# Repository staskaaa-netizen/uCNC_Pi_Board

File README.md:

# uCNC RP2350B Motherboard - MANUFACTURING-READY PROTOTYPE

KiCad 10 carrier for a socketed WeAct Studio RP2350B Core Board. The board
provides isolated machine I/O, motion and encoder interfaces, LCD power,
storage, optional Wi-Fi and analog I/O on a 160 mm x 120 mm two-layer PCB.

**Status: MANUFACTURING PACKAGE GENERATED; FINAL DRC REVIEW REQUIRED.** The
circuit, pin mapping, PCB and manufacturing archives are complete. The PCB
fabrication and SMT assembly ZIPs are generated from the current board.

The current BOM has 263 physical parts in 44 purchasing groups. SMT assembly
contains 227 references in 33 groups; D53 is hand-fit and excluded from the
CPL. The combined JLC BOM contains 262 references in 43 groups.

## Board features

- 16 isolated 24 V PLC inputs, `I01-I16`, with TLP291-4 optocouplers.
- One dedicated isolated E-stop input on GPIO9, outside the shift-register
  chain.
- Four cascaded 74HC165 inputs and four cascaded SN74AHCT595 outputs.
- All 32 input-register channels have 10 k pull-ups, including the direct
  servo ZERO/ERROR inputs.
- Seven STEP/DIR axes, A0-A6, with labels `EN3 STPn DIRn`.
- Seven paired servo ZERO/ERROR inputs with individual 3-pin connectors.
- Two spare U7 register inputs exposed on J55 with 10 k pull-ups.
- All 35 indicator LEDs are green Hubei KENTO `KT-0805G` 0805 parts.
- Two onsemi MC74AC541DWR2G 5 V motion buffers.
- Sixteen optically isolated general outputs, `D01-D16`, driven by two
  TBD62083AFG(Z,EL) arrays.
- Three 5 V encoder interfaces with a 3.3 V logic-side buffer.
- Four 0-10 V analog inputs and four ground-referenced 0-10 V analog outputs.
- MicroSD through J36 or the on-board SOFNG TF-15x15 socket J54.
- Passive HSTX-to-LVDS interface on J22 using two 4 x 330 ohm, 4 x 0603 arrays.
- Optional ESP-01 with a dedicated 3.3 V regulator.
- Isolated 24 V to 12 V backlight supply.

## I/O map

| Function | Signal | Connector mapping |
|---|---|---|
| PLC inputs | `I01-I16` | J7: `I01-I08`; J8: `I09-I16` |
| General outputs | `D01-D16` | J12: `D01-D08`; J32: `D09-D16` |
| Motion A0 | `EN3`, `STP0`, `DIR0` | J10; status J40 |
| Motion A1 | `EN3`, `STP1`, `DIR1` | J11; status J41 |
| Motion A2 | `EN3`, `STP2`, `DIR2` | J28; status J42 |
| Motion A3 | `EN4`, `STP3`, `DIR3` | J29; status J43 |
| Motion A4 | `EN4`, `STP4`, `DIR4` | J47; status J50 |
| Motion A5 | `EN4`, `STP5`, `DIR5` | J46; status J49 |
| Motion A6 | `EN4`, `STP6`, `DIR6` | J30; status J48 |

The isolated logic-side input names are `I01_N-I16_N`. Every motion connector
uses pin 1 for enable, pin 2 for STEP and pin 3 for DIR. Every paired status
connector uses pin 1 for `GND`, pin 2 for ERROR and pin 3 for ZERO.
On the assembled board, motion labels are printed in the opposite physical
reading direction as `DIRn STPn ENx`; the pad-to-net mapping above remains
authoritative.

## Open the project

Open `hardware/motherboard.kicad_pro` in KiCad 10.0 or newer.

- Root schematic: `hardware/motherboard.kicad_sch`
- PCB: `hardware/motherboard.kicad_pcb`
- Local symbols, footprints and 3D models: `hardware/libraries/`
- Manufacturing data: `manufacturing/` (see `manufacturing/README.md`)
- Design notes: `documentation/`

The checked-in KiCad board is authoritative. It contains the approved manual
placement and routing. Do not run a full PCB regeneration over that file.

## Design documentation

- [Board specification](documentation/board-specification.md)
- [GPIO map](documentation/gpio-map.md)
- [Normative HAL pin and function contract](documentation/hal-pinout-contract.md)
- [WeAct RP2350B pin allocation](documentation/rp2350-pinout.md)
- [Input and output bit map](documentation/io-bit-map.md)
- [Signal naming](documentation/naming.md)
- [Connector pinouts](documentation/connectors.md)
- [Power budget](documentation/power-budget.md)
- [PLC inputs](documentation/plc-inputs.md)
- [Decoupling map](documentation/decoupling-map.md)
- [Component placement classes](documentation/component-placement-classes.md)
- [LCD LVDS interface](documentation/display-population.md)
- [Wi-Fi module](documentation/wifi-module.md)
- [Analog calibration](documentation/analog-calibration.md)
- [Four-channel 0-10 V outputs](documentation/analog-outputs.md)
- [uCNC RP2350 compatibility](documentation/ucnc-rp2350.md)
- [Mechanical notes](documentation/mechanical.md)
- [Assembly notes](documentation/assembly-options.md)
- [Release checklist](TODO.md)
- [Design-process retrospective and next-time playbook](documentation/design-process-retrospective.md)

## Manufacturing review files

- [Combined board review](manufacturing/board-review.pdf)
- [Ordered first-batch PCB review](manufacturing/board-ordered-first-batch.jpg)
- [Board specification PDF](manufacturing/board-specification.pdf)
- [Front artwork and assembly layer](manufacturing/board-front.pdf)
- [Mirrored rear artwork](manufacturing/board-back.pdf)
- [Current top 3D render](manufacturing/board-3d-top-da42d9de.png)
- [Current bottom 3D render](manufacturing/board-3d-bottom-da42d9de.png)
- [Connector label orientation check](manufacturing/connector-label-check.png)
- [Complete grouped BOM](manufacturing/bom.csv)
- [SMT-only grouped BOM](manufacturing/bom-smt.csv)
- [SMT-only reference BOM](manufacturing/bom-smt-refs.csv)
- [JLCPCB-format grouped BOM](manufacturing/bom-jlcpcb.csv)
- [JLCPCB stock and Basic/Extended audit](manufacturing/jlcpcb-stock-audit.csv)
- [Non-SMT grouped BOM](manufacturing/bom-non-smt.csv)
- [Combined SMT and non-SMT BOM](manufacturing/bom-all-jlcpcb.csv)
- [Pick-and-place CPL](manufacturing/cpl-jlcpcb.csv)
- [PCB fabrication ZIP](manufacturing/uCNC_Pi_Board_PCB_Fabrication.zip)
- [PCB fabrication + SMT assembly ZIP](manufacturing/uCNC_Pi_Board_SMT_Assembly.zip)

## Verification status

The current netlist contains 274 schematic components in 321 nets. The PCB has
268 footprints, 2,221 routed track segments and 232 vias. DRC reports zero
unconnected items, no copper-clearance errors and eight silkscreen warnings.
ERC has no electrical errors and 35 library-symbol cache warnings.

This is a routed prototype manufacturing package. It is not a safety-rated
controller. Hazardous energy removal must remain an independent hard-wired
safety function and must be validated in the complete machine.

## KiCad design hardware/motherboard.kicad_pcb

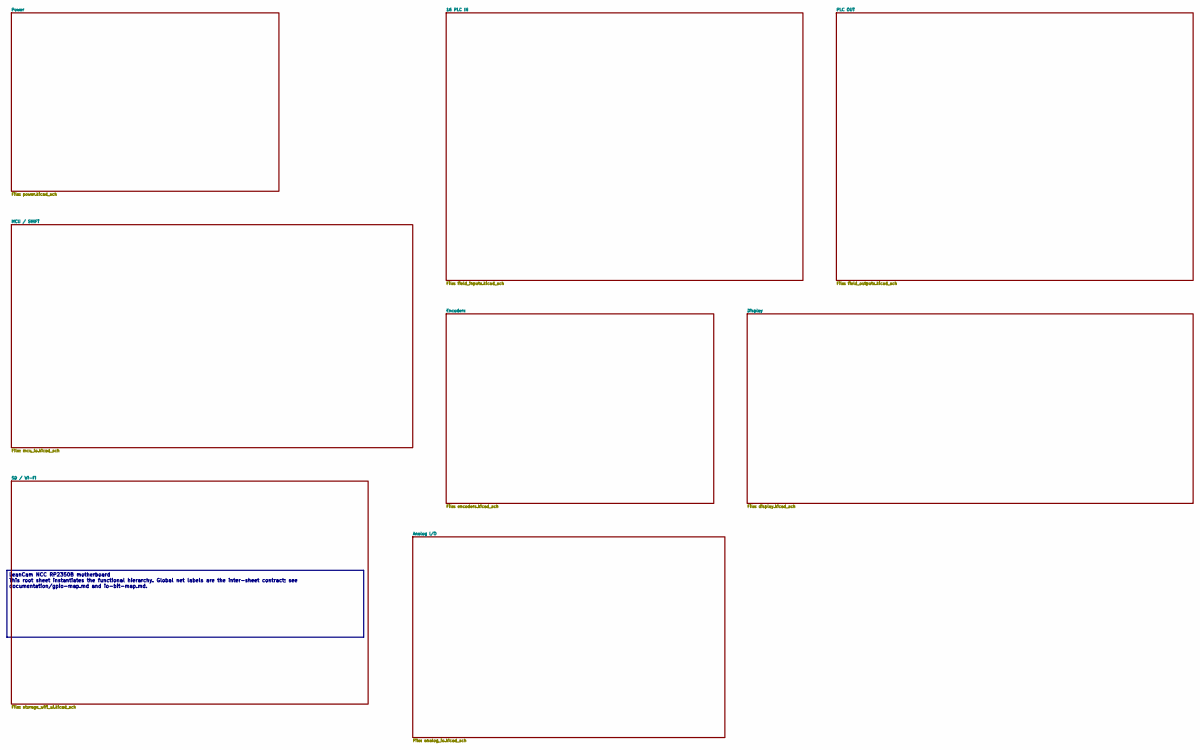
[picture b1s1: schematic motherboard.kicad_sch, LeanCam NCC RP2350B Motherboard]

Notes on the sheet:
LeanCam NCC RP2350B motherboard This root sheet instantiates the functional hierarchy. Global net labels are the inter-sheet contract; see documentation/gpio-map.md and io-bit-map.md.

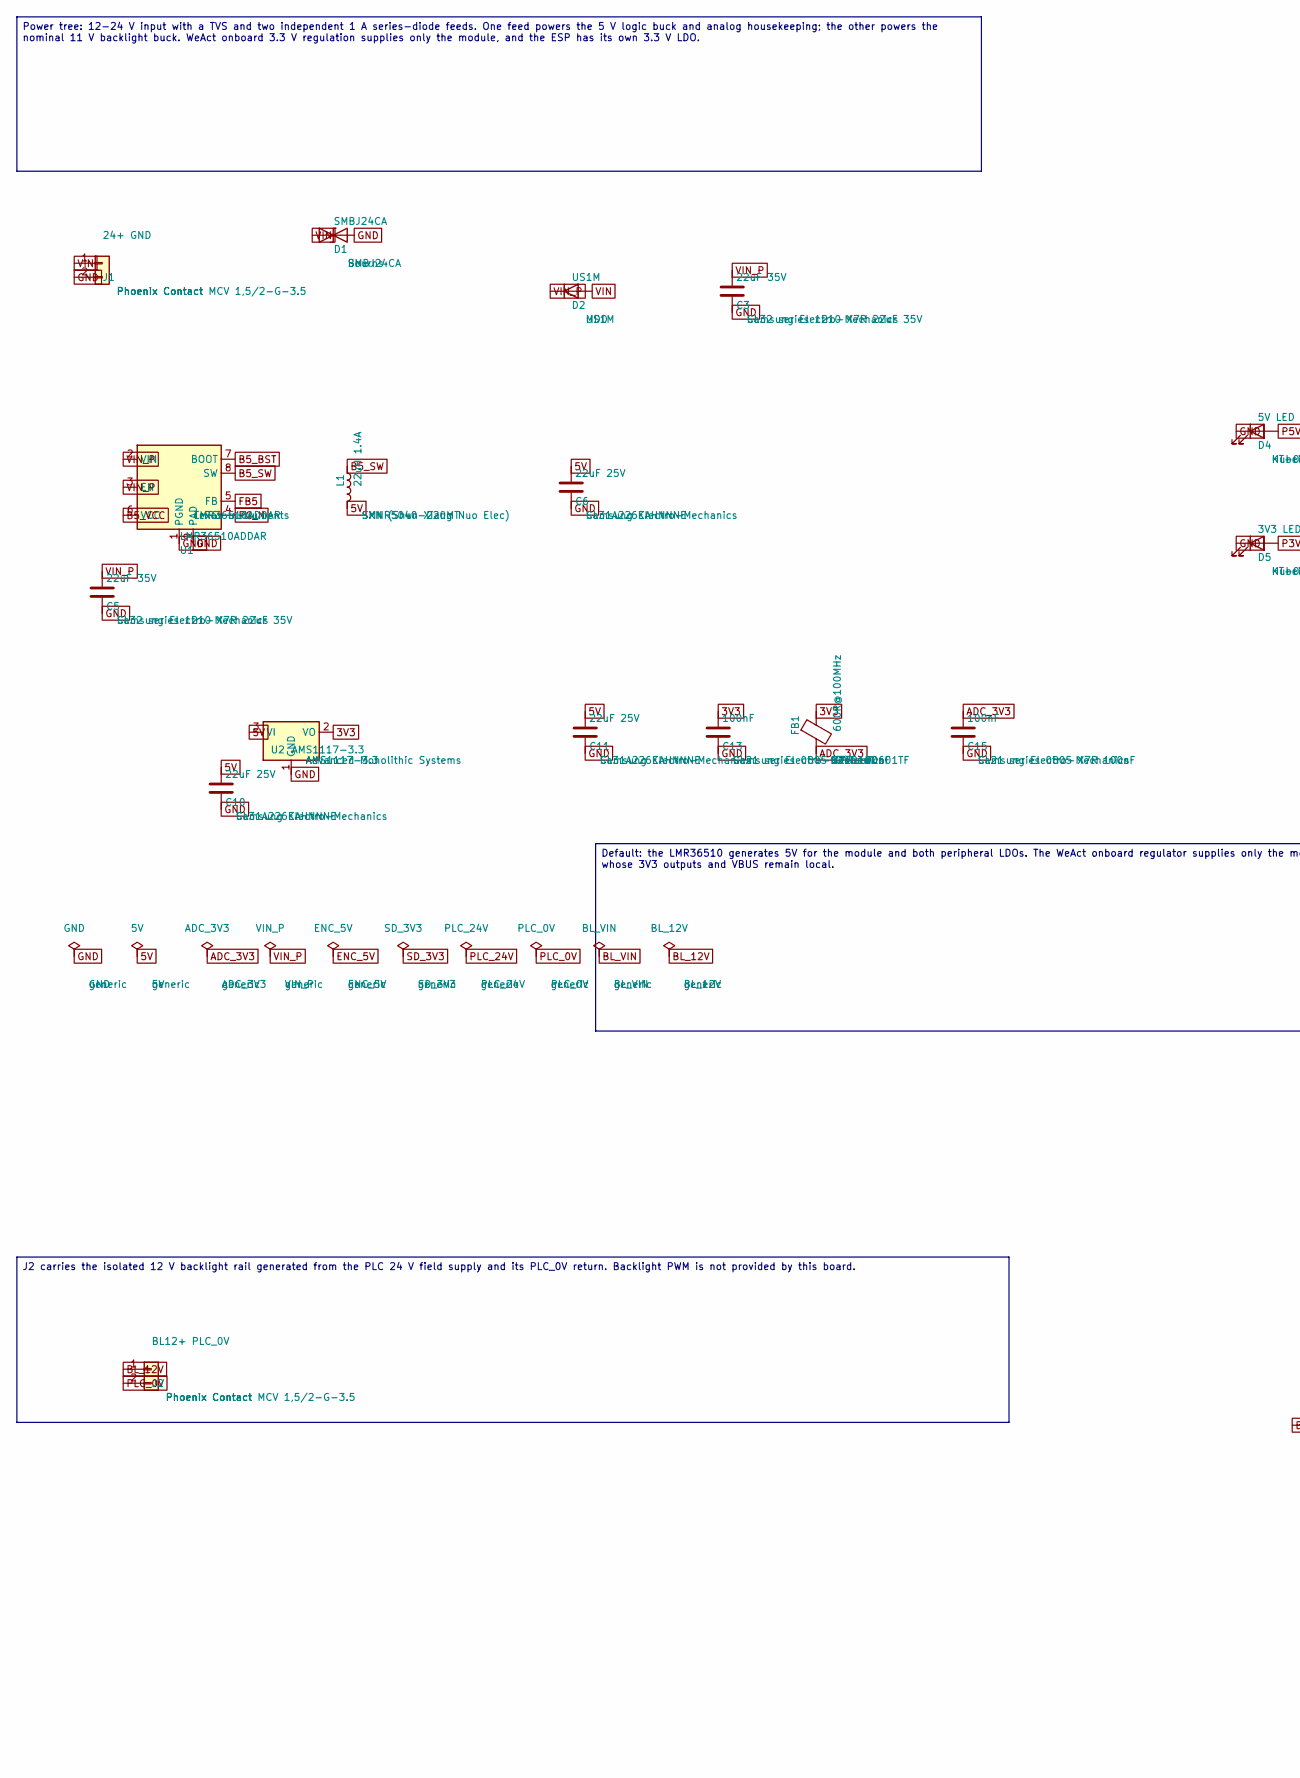
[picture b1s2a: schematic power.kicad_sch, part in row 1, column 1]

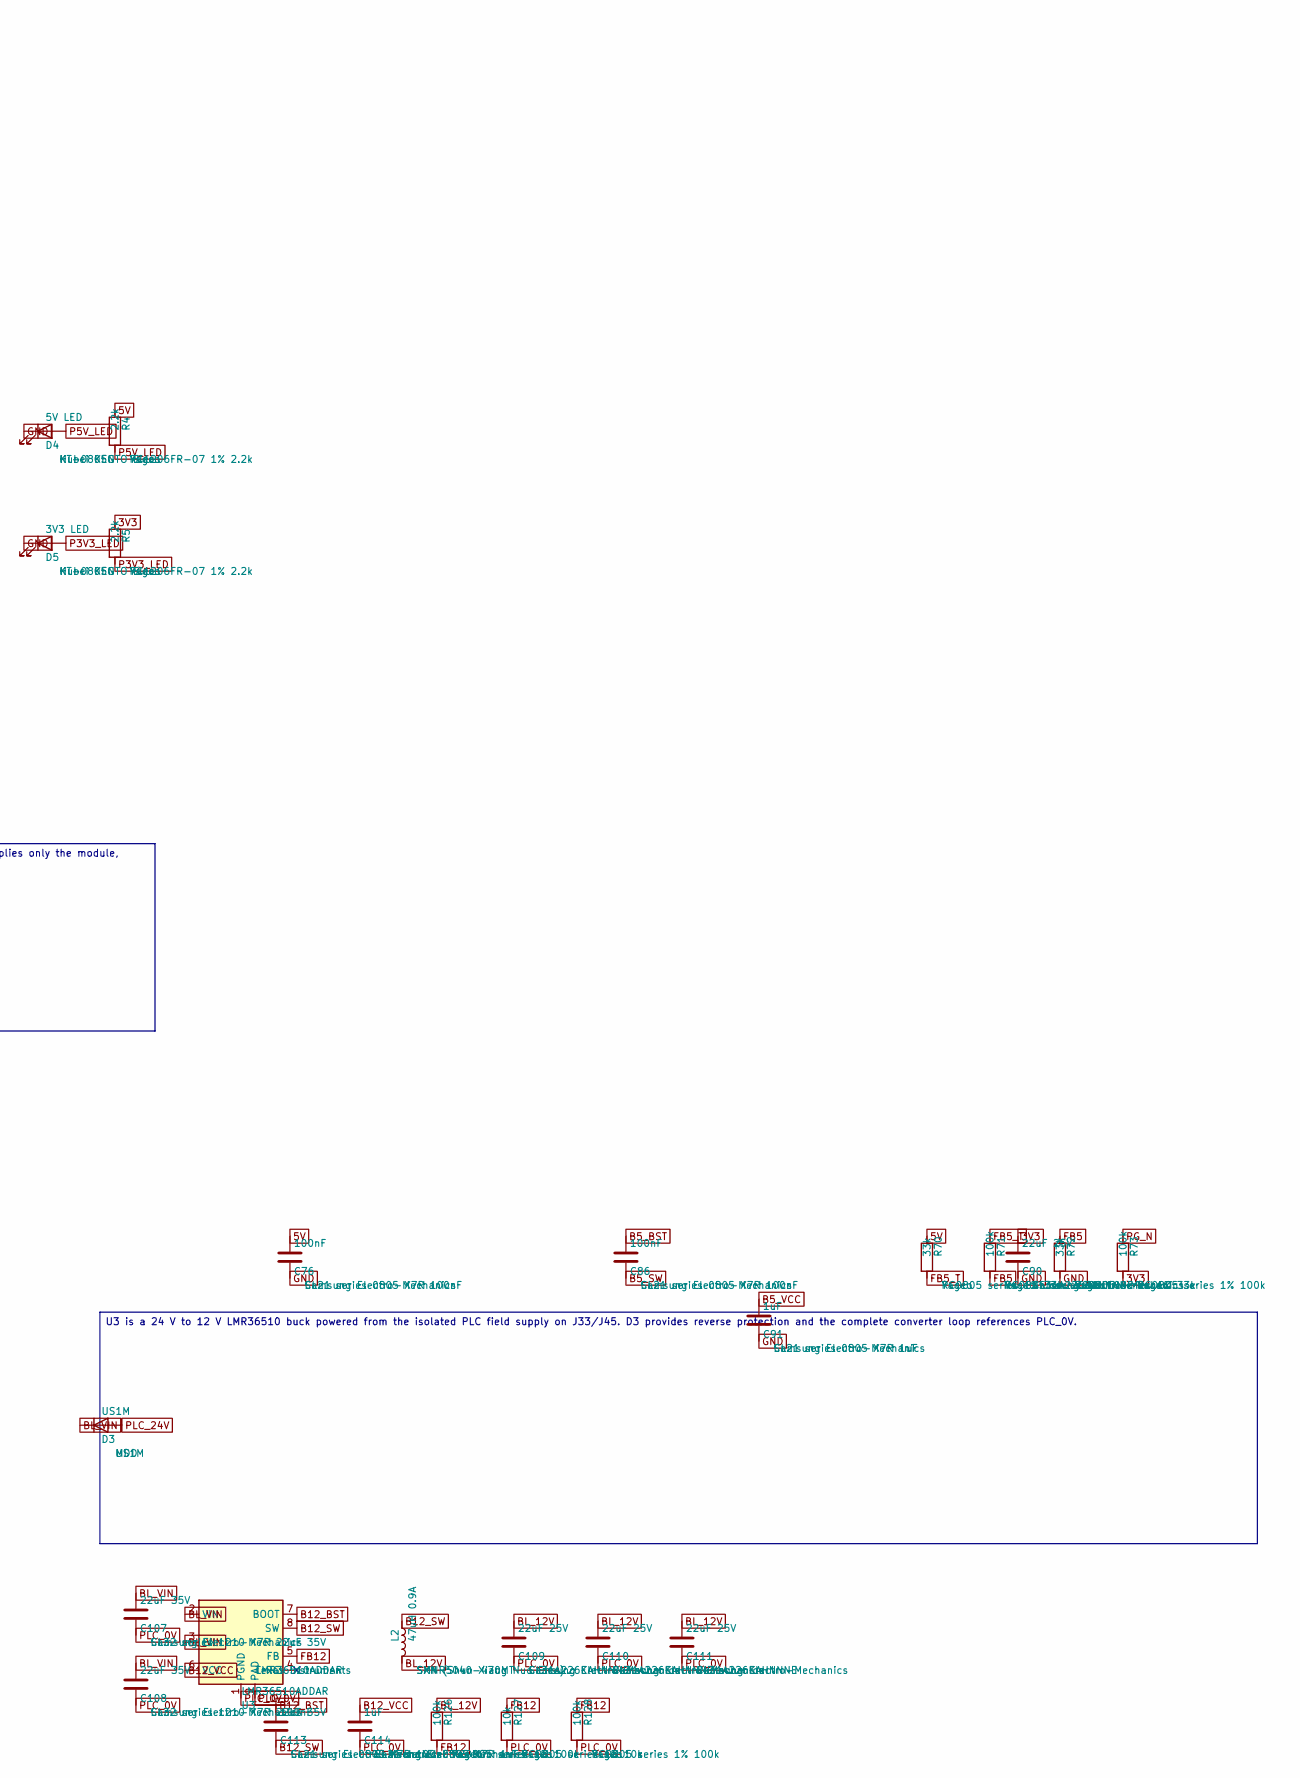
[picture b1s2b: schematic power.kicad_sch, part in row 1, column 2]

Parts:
C3, C5, C107, C108: 22uF 35V; C_1210_3225Metric; MPN CL32 series 1210 X7R 22uF 35V
C6, C10, C11, C90, C109, C110, C111: 22uF 25V; C_1206_3216Metric; MPN CL31A226KAHNNNE
C13, C15, C76, C86, C113: 100nF; C_0805_2012Metric; MPN CL21 series 0805 X7R 100nF
C91, C114: 1uF; C_0805_2012Metric; MPN CL21 series 0805 X7R 1uF
D1: SMBJ24CA; D_SMB; MPN SMBJ24CA
D2, D3: US1M; D_SMA; MPN US1M
D4: 5V LED; LED_0805_2012Metric; MPN KT-0805G
D5: 3V3 LED; LED_0805_2012Metric; MPN KT-0805G
FB1: 600R@100MHz; R_0805_2012Metric; MPN GZ2012D601TF
FLG1: GND; MPN GND
FLG2: 5V; MPN 5V
FLG3: ADC_3V3; MPN ADC_3V3
FLG4: VIN_P; MPN VIN_P
FLG5: ENC_5V; MPN ENC_5V
FLG6: SD_3V3; MPN SD_3V3
FLG7: PLC_24V; MPN PLC_24V
FLG8: PLC_0V; MPN PLC_0V
FLG9: BL_VIN; MPN BL_VIN
FLG10: BL_12V; MPN BL_12V
J1: 24+ GND; PhoenixContact_MCV_1,5_2-G-3.5_1x02_P3.50mm_Vertical; MPN Phoenix Contact MCV 1,5/2-G-3.5
J2: BL12+ PLC_0V; PhoenixContact_MCV_1,5_2-G-3.5_1x02_P3.50mm_Vertical; MPN Phoenix Contact MCV 1,5/2-G-3.5
L1: 22uH 1.4A; L_SXN_SMNR5040; MPN SMNR5040-220MT
L2: 47uH 0.9A; L_SXN_SMNR5040; MPN SMNR5040-470MT
R4, R5: 2.2k; R_1206_3216Metric; MPN RC1206FR-07 1% 2.2k
R70, R72: 33k; R_0805_2012Metric; MPN RC0805 series 1% 33k
R71, R73, R126, R128: 100k; R_0805_2012Metric; MPN RC0805 series 1% 100k
R127: 10k; R_0805_2012Metric; MPN RC0805 series 1% 10k
U1, U3: LMR36510ADDAR; SOIC-8-1EP_3.9x4.9mm_P1.27mm_EP2.41x3.3mm; MPN LMR36510ADDAR
U2: AMS1117-3.3; SOT-223-3_TabPin2; MPN AMS1117-3.3

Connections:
3V3: C13.1, C90.1, FB1.1, R5.1, R73.2, U2.2 (VO); also elsewhere on the board
5V: C6.1, C10.1, C11.1, C76.1, FLG2.1, L1.2, R4.1, R70.1, U2.3 (VI); also elsewhere on the board
ADC_3V3: C15.1, FB1.2, FLG3.1; also elsewhere on the board
B5_BST: C86.1, U1.7 (BOOT)
B5_SW: C86.2, L1.1, U1.8 (SW)
B5_VCC: C91.1, U1.6 (VCC)
B12_BST: C113.1, U3.7 (BOOT)
B12_SW: C113.2, L2.1, U3.8 (SW)
B12_VCC: C114.1, U3.6 (VCC)
BL_12V: C109.1, C110.1, C111.1, FLG10.1, J2.1, L2.2, R126.1
BL_VIN: C107.1, C108.1, D3.1 (K), FLG9.1, U3.2 (VIN), U3.3 (EN)
FB5: R71.2, R72.1, U1.5 (FB)
FB5_T: R70.2, R71.1
FB12: R126.2, R127.1, R128.1, U3.5 (FB)
GND: C3.2, C5.2, C6.2, C10.2, C11.2, C13.2, C15.2, C76.2, C90.2, C91.2, D1.2 (A2), D4.1 (K), D5.1 (K), FLG1.1, J1.2, R72.2, U1.1 (PGND), U1.9 (PAD), U2.1 (GND); also elsewhere on the board
P3V3_LED: D5.2 (A), R5.2
P5V_LED: D4.2 (A), R4.2
PG_N: R73.1, U1.4 (PG); also elsewhere on the board
PLC_0V: C107.2, C108.2, C109.2, C110.2, C111.2, C114.2, FLG8.1, J2.2, R127.2, R128.2, U3.1 (PGND), U3.9 (PAD); also elsewhere on the board
PLC_24V: D3.2 (A), FLG7.1; also elsewhere on the board
VIN: D1.1 (A1), D2.2 (A), J1.1
VIN_P: C3.1, C5.1, D2.1 (K), FLG4.1, U1.2 (VIN), U1.3 (EN); also elsewhere on the board

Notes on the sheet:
Power tree: 12-24 V input with a TVS and two independent 1 A series-diode feeds. One feed powers the 5 V logic buck and analog housekeeping; the other powers the nominal 11 V backlight buck. WeAct onboard 3.3 V regulation supplies only the module, and the ESP has its own 3.3 V LDO.
Default: the LMR36510 generates 5V for the module and both peripheral LDOs. The WeAct onboard regulator supplies only the module, whose 3V3 outputs and VBUS remain local.
J2 carries the isolated 12 V backlight rail generated from the PLC 24 V field supply and its PLC_0V return. Backlight PWM is not provided by this board.
U3 is a 24 V to 12 V LMR36510 buck powered from the isolated PLC field supply on J33/J45. D3 provides reverse protection and the complete converter loop references PLC_0V.

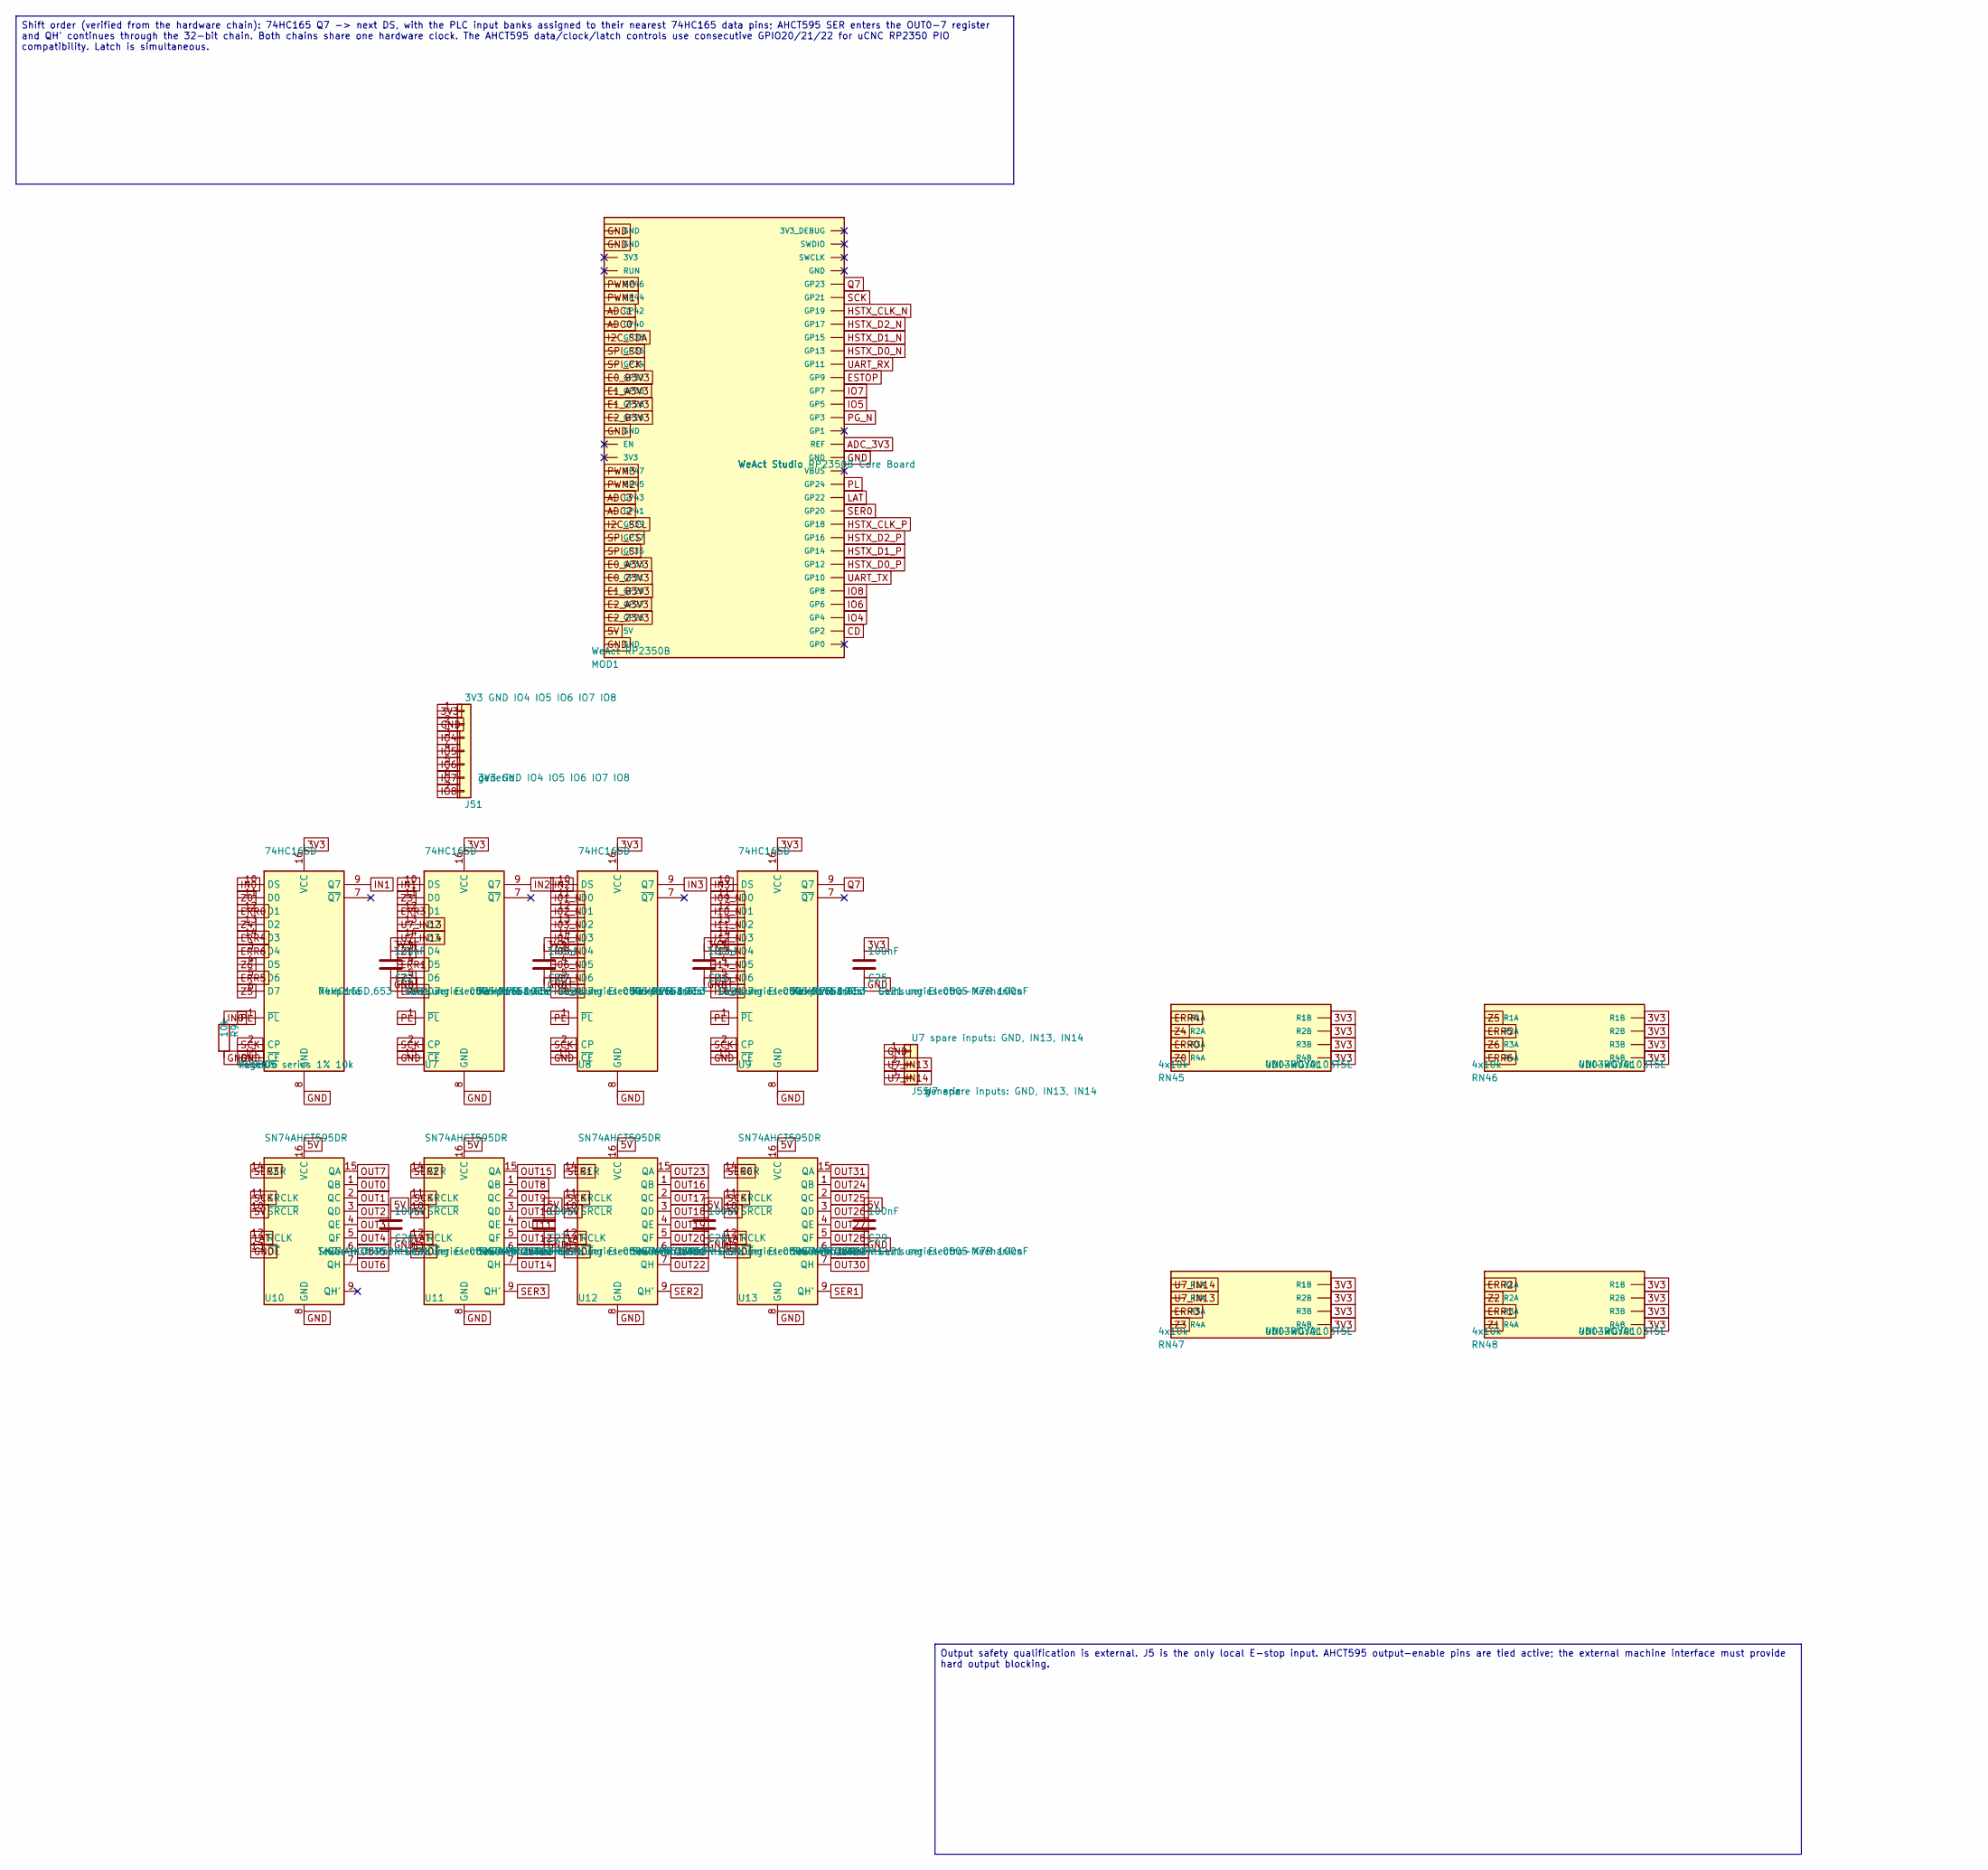
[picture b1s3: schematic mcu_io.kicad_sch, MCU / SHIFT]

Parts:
C22, C23, C24, C25, C26, C27, C28, C29: 100nF; C_0805_2012Metric; MPN CL21 series 0805 X7R 100nF
J51: 3V3 GND IO4 IO5 IO6 IO7 IO8; PinSocket_1x07_P2.54mm_Vertical; MPN 3V3 GND IO4 IO5 IO6 IO7 IO8
J55: U7 spare inputs: GND, IN13, IN14; PinHeader_1x03_P2.54mm_Vertical; MPN U7 spare inputs: GND, IN13, IN14
MOD1: WeAct RP2350B; WeAct_RP2350B_Socket; MPN WeAct Studio RP2350B Core Board
R9: 10k; R_0805_2012Metric; MPN RC0805 series 1% 10k
RN45, RN46, RN47, RN48: 4x10k; R_Array_Convex_4x0603; MPN 4D03WGJ0103T5E
U6, U7, U8, U9: 74HC165D; SOIC-16_3.9x9.9mm_P1.27mm; MPN 74HC165D,653
U10, U11, U12, U13: SN74AHCT595DR; SOIC-16_3.9x9.9mm_P1.27mm; MPN SN74AHCT595DR

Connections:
3V3: C22.1, C23.1, C24.1, C25.1, J51.1, RN45.5 (R4B), RN45.6 (R3B), RN45.7 (R2B), RN45.8 (R1B), RN46.5 (R4B), RN46.6 (R3B), RN46.7 (R2B), RN46.8 (R1B), RN47.5 (R4B), RN47.6 (R3B), RN47.7 (R2B), RN47.8 (R1B), RN48.5 (R4B), RN48.6 (R3B), RN48.7 (R2B), RN48.8 (R1B), U6.16 (VCC), U7.16 (VCC), U8.16 (VCC), U9.16 (VCC); also elsewhere on the board
5V: C26.1, C27.1, C28.1, C29.1, MOD1.31 (5V), U10.10 (~SRCLR), U10.16 (VCC), U11.10 (~SRCLR), U11.16 (VCC), U12.10 (~SRCLR), U12.16 (VCC), U13.10 (~SRCLR), U13.16 (VCC); also elsewhere on the board
ADC0: MOD1.8 (GP40); also elsewhere on the board
ADC1: MOD1.7 (GP42); also elsewhere on the board
ADC2: MOD1.22 (GP41); also elsewhere on the board
ADC3: MOD1.21 (GP43); also elsewhere on the board
ADC_3V3: MOD1.48 (REF); also elsewhere on the board
CD: MOD1.34 (GP2); also elsewhere on the board
E0_A3V3: MOD1.26 (GP33); also elsewhere on the board
E0_B3V3: MOD1.12 (GP32); also elsewhere on the board
E0_Z3V3: MOD1.27 (GP31); also elsewhere on the board
E1_A3V3: MOD1.13 (GP30); also elsewhere on the board
E1_B3V3: MOD1.28 (GP29); also elsewhere on the board
E1_Z3V3: MOD1.14 (GP28); also elsewhere on the board
E2_A3V3: MOD1.29 (GP27); also elsewhere on the board
E2_B3V3: MOD1.15 (GP26); also elsewhere on the board
E2_Z3V3: MOD1.30 (GP25); also elsewhere on the board
ERR0: RN45.3 (R3A), U6.12 (D1); also elsewhere on the board
ERR1: RN48.3 (R3A), U7.4 (D5); also elsewhere on the board
ERR2: RN48.1 (R1A), U7.6 (D7); also elsewhere on the board
ERR3: RN47.3 (R3A), U7.12 (D1); also elsewhere on the board
ERR4: RN45.1 (R1A), U6.14 (D3); also elsewhere on the board
ERR5: RN46.2 (R2A), U6.5 (D6); also elsewhere on the board
ERR6: RN46.4 (R4A), U6.3 (D4); also elsewhere on the board
ESTOP: MOD1.53 (GP9); also elsewhere on the board
GND: C22.2, C23.2, C24.2, C25.2, C26.2, C27.2, C28.2, C29.2, J51.2, J55.1, MOD1.1 (GND), MOD1.2 (GND), MOD1.16 (GND), MOD1.32 (GND), MOD1.47 (GND), R9.2, U6.8 (GND), U6.15 (~CE), U7.8 (GND), U7.15 (~CE), U8.8 (GND), U8.15 (~CE), U9.8 (GND), U9.15 (~CE), U10.8 (GND), U10.13 (~OE), U11.8 (GND), U11.13 (~OE), U12.8 (GND), U12.13 (~OE), U13.8 (GND), U13.13 (~OE); also elsewhere on the board
HSTX_CLK_N: MOD1.58 (GP19); also elsewhere on the board
HSTX_CLK_P: MOD1.42 (GP18); also elsewhere on the board
HSTX_D0_N: MOD1.55 (GP13); also elsewhere on the board
HSTX_D0_P: MOD1.39 (GP12); also elsewhere on the board
HSTX_D1_N: MOD1.56 (GP15); also elsewhere on the board
HSTX_D1_P: MOD1.40 (GP14); also elsewhere on the board
HSTX_D2_N: MOD1.57 (GP17); also elsewhere on the board
HSTX_D2_P: MOD1.41 (GP16); also elsewhere on the board
I01_N: U8.11 (D0); also elsewhere on the board
I2C_SCL: MOD1.23 (GP39); also elsewhere on the board
I2C_SDA: MOD1.9 (GP38); also elsewhere on the board
I02_N: U8.12 (D1); also elsewhere on the board
I03_N: U8.13 (D2); also elsewhere on the board
I04_N: U8.14 (D3); also elsewhere on the board
I05_N: U8.3 (D4); also elsewhere on the board
I06_N: U8.4 (D5); also elsewhere on the board
I07_N: U8.5 (D6); also elsewhere on the board
I08_N: U8.6 (D7); also elsewhere on the board
I09_N: U9.11 (D0); also elsewhere on the board
I10_N: U9.12 (D1); also elsewhere on the board
I11_N: U9.13 (D2); also elsewhere on the board
I12_N: U9.14 (D3); also elsewhere on the board
I13_N: U9.3 (D4); also elsewhere on the board
I14_N: U9.4 (D5); also elsewhere on the board
I15_N: U9.5 (D6); also elsewhere on the board
I16_N: U9.6 (D7); also elsewhere on the board
IN0: R9.1, U6.10 (DS)
IN1: U6.9 (Q7), U7.10 (DS)
IN2: U7.9 (Q7), U8.10 (DS)
IN3: U8.9 (Q7), U9.10 (DS)
IO4: J51.3, MOD1.35 (GP4)
IO5: J51.4, MOD1.51 (GP5)
IO6: J51.5, MOD1.36 (GP6)
IO7: J51.6, MOD1.52 (GP7)
IO8: J51.7, MOD1.37 (GP8)
LAT: MOD1.44 (GP22), U10.12 (RCLK), U11.12 (RCLK), U12.12 (RCLK), U13.12 (RCLK)
OUT0: U10.1 (QB); also elsewhere on the board
OUT1: U10.2 (QC); also elsewhere on the board
OUT2: U10.3 (QD); also elsewhere on the board
OUT3: U10.4 (QE); also elsewhere on the board
OUT4: U10.5 (QF); also elsewhere on the board
OUT5: U10.6 (QG); also elsewhere on the board
OUT6: U10.7 (QH); also elsewhere on the board
OUT7: U10.15 (QA); also elsewhere on the board
OUT8: U11.1 (QB); also elsewhere on the board
OUT9: U11.2 (QC); also elsewhere on the board
OUT10: U11.3 (QD); also elsewhere on the board
OUT11: U11.4 (QE); also elsewhere on the board
OUT12: U11.5 (QF); also elsewhere on the board
OUT13: U11.6 (QG); also elsewhere on the board
OUT14: U11.7 (QH); also elsewhere on the board
OUT15: U11.15 (QA); also elsewhere on the board
OUT16: U12.1 (QB); also elsewhere on the board
OUT17: U12.2 (QC); also elsewhere on the board
OUT18: U12.3 (QD); also elsewhere on the board
OUT19: U12.4 (QE); also elsewhere on the board
OUT20: U12.5 (QF); also elsewhere on the board
OUT21: U12.6 (QG); also elsewhere on the board
OUT22: U12.7 (QH); also elsewhere on the board
OUT23: U12.15 (QA); also elsewhere on the board
OUT24: U13.1 (QB); also elsewhere on the board
OUT25: U13.2 (QC); also elsewhere on the board
OUT26: U13.3 (QD); also elsewhere on the board
OUT27: U13.4 (QE); also elsewhere on the board
OUT28: U13.5 (QF); also elsewhere on the board
OUT29: U13.6 (QG); also elsewhere on the board
OUT30: U13.7 (QH); also elsewhere on the board
OUT31: U13.15 (QA); also elsewhere on the board
PG_N: MOD1.50 (GP3); also elsewhere on the board
PL: MOD1.45 (GP24), U6.1 (~PL), U7.1 (~PL), U8.1 (~PL), U9.1 (~PL)
PWM0: MOD1.5 (GP46); also elsewhere on the board
PWM1: MOD1.6 (GP44); also elsewhere on the board
PWM2: MOD1.20 (GP45); also elsewhere on the board
PWM3: MOD1.19 (GP47); also elsewhere on the board
Q7: MOD1.60 (GP23), U9.9 (Q7)
SCK: MOD1.59 (GP21), U6.2 (CP), U7.2 (CP), U8.2 (CP), U9.2 (CP), U10.11 (SRCLK), U11.11 (SRCLK), U12.11 (SRCLK), U13.11 (SRCLK)
SER0: MOD1.43 (GP20), U13.14 (SER)
SER1: U12.14 (SER), U13.9 (QH')
SER2: U11.14 (SER), U12.9 (QH')
SER3: U10.14 (SER), U11.9 (QH')
SPI_CK: MOD1.11 (GP34); also elsewhere on the board
SPI_CS: MOD1.24 (GP37); also elsewhere on the board
SPI_SI: MOD1.25 (GP35); also elsewhere on the board
SPI_SO: MOD1.10 (GP36); also elsewhere on the board
U7_IN13: J55.2, RN47.2 (R2A), U7.13 (D2)
U7_IN14: J55.3, RN47.1 (R1A), U7.14 (D3)
UART_RX: MOD1.54 (GP11); also elsewhere on the board
UART_TX: MOD1.38 (GP10); also elsewhere on the board
Z0: RN45.4 (R4A), U6.11 (D0); also elsewhere on the board
Z1: RN48.4 (R4A), U7.3 (D4); also elsewhere on the board
Z2: RN48.2 (R2A), U7.5 (D6); also elsewhere on the board
Z3: RN47.4 (R4A), U7.11 (D0); also elsewhere on the board
Z4: RN45.2 (R2A), U6.13 (D2); also elsewhere on the board
Z5: RN46.1 (R1A), U6.6 (D7); also elsewhere on the board
Z6: RN46.3 (R3A), U6.4 (D5); also elsewhere on the board

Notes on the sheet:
Shift order (verified from the hardware chain): 74HC165 Q7 -> next DS, with the PLC input banks assigned to their nearest 74HC165 data pins; AHCT595 SER enters the OUT0-7 register and QH' continues through the 32-bit chain. Both chains share one hardware clock. The AHCT595 data/clock/latch controls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
Output safety qualification is external. J5 is the only local E-stop input. AHCT595 output-enable pins are tied active; the external machine interface must provide hard output blocking.
